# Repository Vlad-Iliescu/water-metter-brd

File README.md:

# water-metter-brd 

full board for capturing water meter image and sending it via wi-fi

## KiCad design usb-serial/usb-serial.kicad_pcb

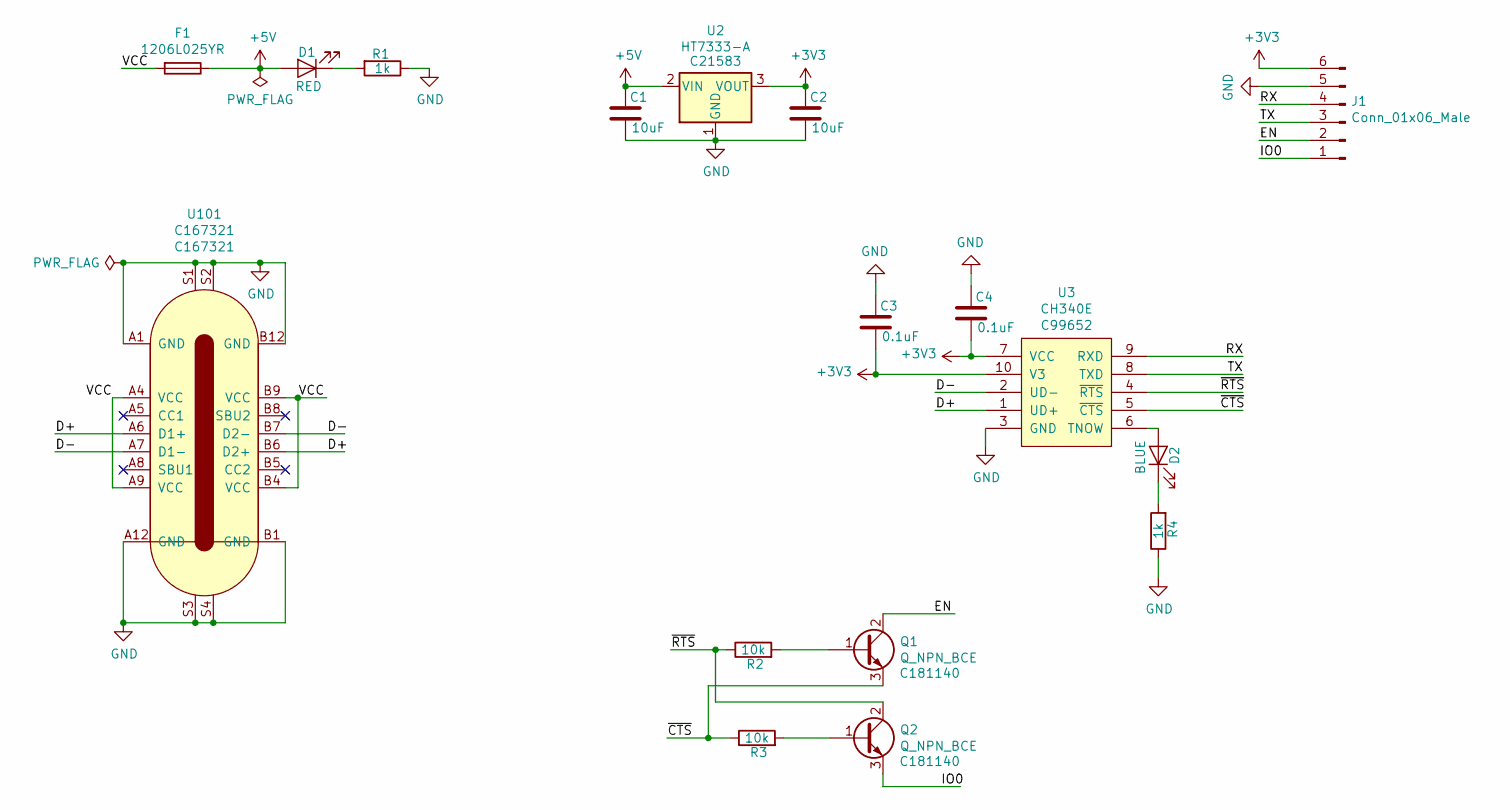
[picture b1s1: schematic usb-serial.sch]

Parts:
C1, C2: 10uF; C_0805_2012Metric
C3, C4: 0.1uF; C_0805_2012Metric
D1: RED; LED_0805_2012Metric
D2: BLUE; LED_0805_2012Metric
F1: 1206L025YR; SMD0805-020-16V; LCSC C99561
J1: Conn_01x06_Male; PinHeader_1x06_P2.54mm_Vertical
Q1, Q2: Q_NPN_BCE; SOT-23; LCSC C181140
R1, R4: 1k; R_0805_2012Metric
R2, R3: 10k; R_0805_2012Metric
U2: HT7333-A; SOT-89-3_Handsoldering; LCSC C21583
U3: CH340E; CH340E-MSOP-10; LCSC C99652
U101: C167321; LCSC C167321

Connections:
+3V3: C2.1, C3.2, C4.2, J1.6, U2.3 (VOUT), U3.7 (VCC), U3.10 (V3)
+5V: C1.1, D1.2 (A), F1.1, U2.2 (VIN)
/D+: U3.1 (UD+), U101.A6 (D1+), U101.B6 (D2+)
/D-: U3.2 (UD-), U101.A7 (D1-), U101.B7 (D2-)
/EN: J1.2, Q1.2 (C)
/IO0: J1.1, Q2.3 (E)
/RX: J1.4, U3.9 (RXD)
/TX: J1.3, U3.8 (TXD)
/VCC: F1.2, U101.A4 (VCC), U101.A9 (VCC), U101.B4 (VCC), U101.B9 (VCC)
/~CTS: Q1.3 (E), R3.1, U3.5 (~CTS~)
/~RTS: Q2.2 (C), R2.1, U3.4 (~RTS~)
GND: C1.2, C2.2, C3.1, C4.1, J1.5, R1.1, R4.1, U2.1 (GND), U3.3 (GND), U101.A1 (GND), U101.A12 (GND), U101.B1 (GND), U101.B12 (GND), U101.S1, U101.S2, U101.S3, U101.S4
unnamed: D1.1 (K), R1.2
unnamed: D2.1 (K), R4.2
unnamed: D2.2 (A), U3.6 (TNOW)
unnamed: Q1.1 (B), R2.2
unnamed: Q2.1 (B), R3.2

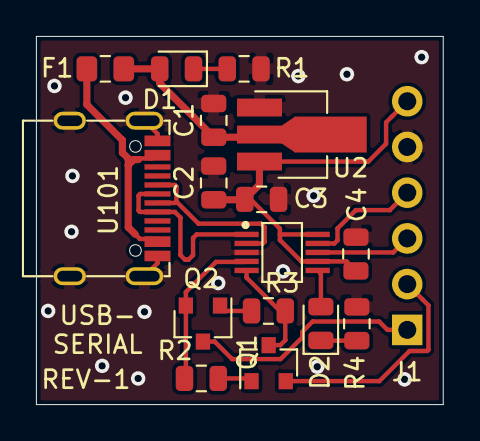
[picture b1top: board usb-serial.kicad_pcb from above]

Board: 2 copper layers, 22.6 x 20.5 mm, 17 parts (1 on the bottom side), 17 nets.

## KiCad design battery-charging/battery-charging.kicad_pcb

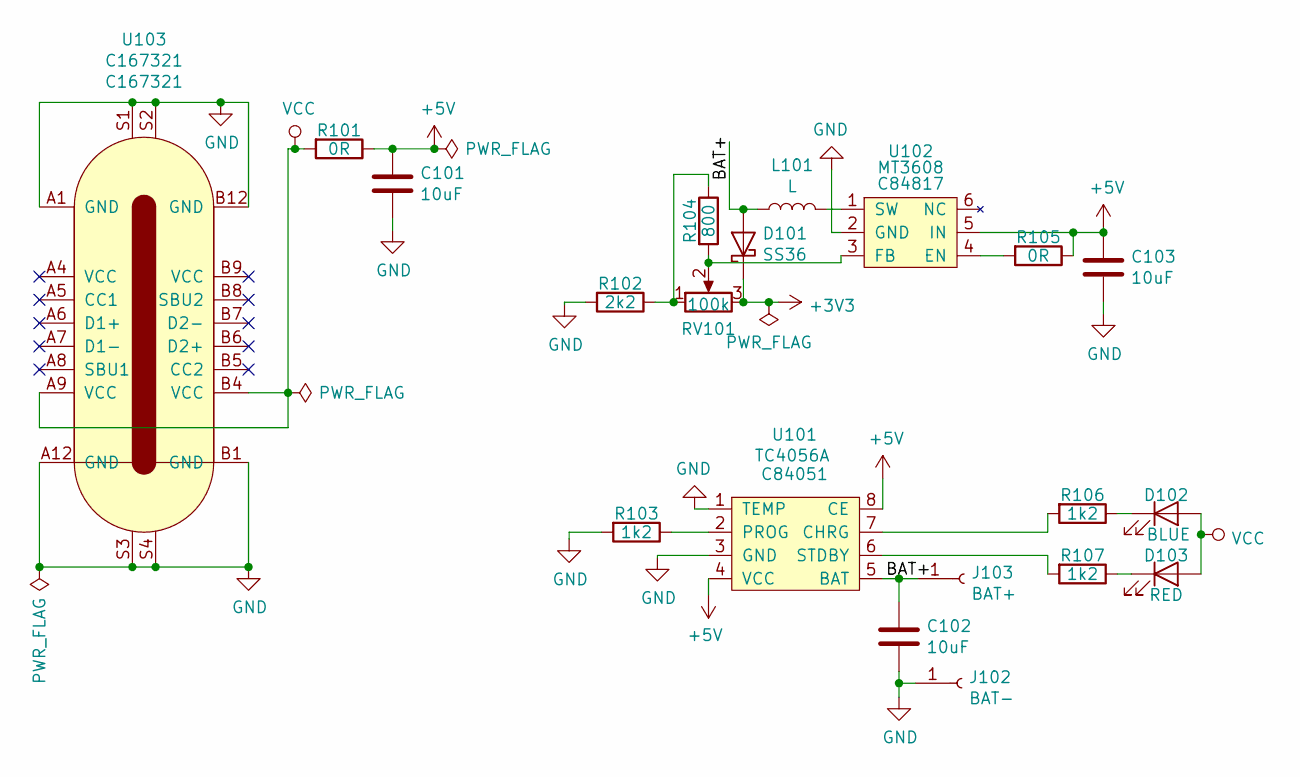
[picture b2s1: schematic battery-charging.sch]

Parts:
C101, C102, C103: 10uF; C_0805_2012Metric_Pad1.15x1.40mm_HandSolder
D101: SS36; D_SMA
D102: BLUE; LED_0805_2012Metric_Pad1.15x1.40mm_HandSolder
D103: RED; LED_0805_2012Metric_Pad1.15x1.40mm_HandSolder
J102: BAT-; PinHeader_1x01_P1.27mm_Vertical
J103: BAT+; PinHeader_1x01_P1.27mm_Vertical
L101: L; L_6.3x6.3_H3
R101, R105: 0R; R_0805_2012Metric_Pad1.15x1.40mm_HandSolder
R102: 2k2; R_0805_2012Metric_Pad1.15x1.40mm_HandSolder
R103, R106, R107: 1k2; R_0805_2012Metric_Pad1.15x1.40mm_HandSolder
R104: 800; R_0805_2012Metric_Pad1.15x1.40mm_HandSolder
RV101: 100k; Potentiometer_Bourns_3296W_Vertical
U101: TC4056A; SOP-8-1EP_4.57x4.57mm_P1.27mm_EP4.57x4.45mm_ThermalVias; LCSC C84051
U102: MT3608; SOT-23-6_Handsoldering; LCSC C84817
U103: C167321; LCSC C167321

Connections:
+3V3: D101.1 (K), RV101.3
+5V: C101.1, C103.1, R101.1, R105.1, U101.4 (VCC), U101.8 (CE), U102.5 (IN)
/BAT+: C102.1, D101.2 (A), J103.1, L101.1, U101.5 (BAT)
GND: C101.2, C102.2, C103.2, J102.1, R102.2, R103.2, U101.1 (TEMP), U101.3 (GND), U102.2 (GND), U103.A1 (GND), U103.A12 (GND), U103.B1 (GND), U103.B12 (GND), U103.S1, U103.S2, U103.S3, U103.S4
unnamed: D102.1 (K), R106.1
unnamed: D103.1 (K), R107.1
unnamed: L101.2, U102.1 (SW)
unnamed: R102.1, R104.1, RV101.1
unnamed: R103.1, U101.2 (PROG)
unnamed: R104.2, RV101.2, U102.3 (FB)
unnamed: R105.2, U102.4 (EN)
unnamed: R106.2, U101.7 (CHRG)
unnamed: R107.2, U101.6 (STDBY)
VCC: D102.2 (A), D103.2 (A), R101.2, U103.A9 (VCC), U103.B4 (VCC)

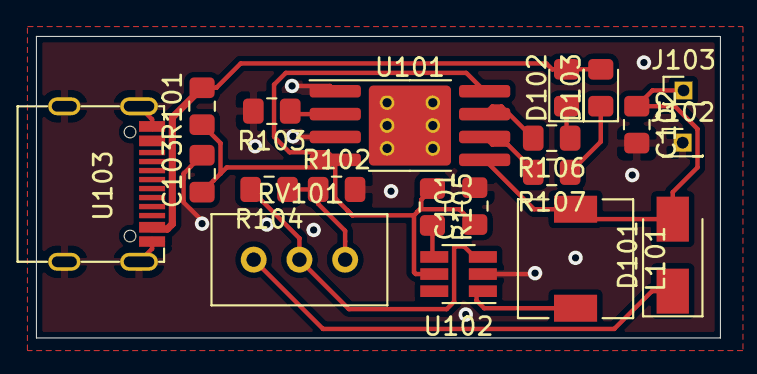
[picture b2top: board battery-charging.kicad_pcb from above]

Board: 2 copper layers, 38.0 x 16.8 mm, 20 parts (0 on the bottom side), 14 nets.

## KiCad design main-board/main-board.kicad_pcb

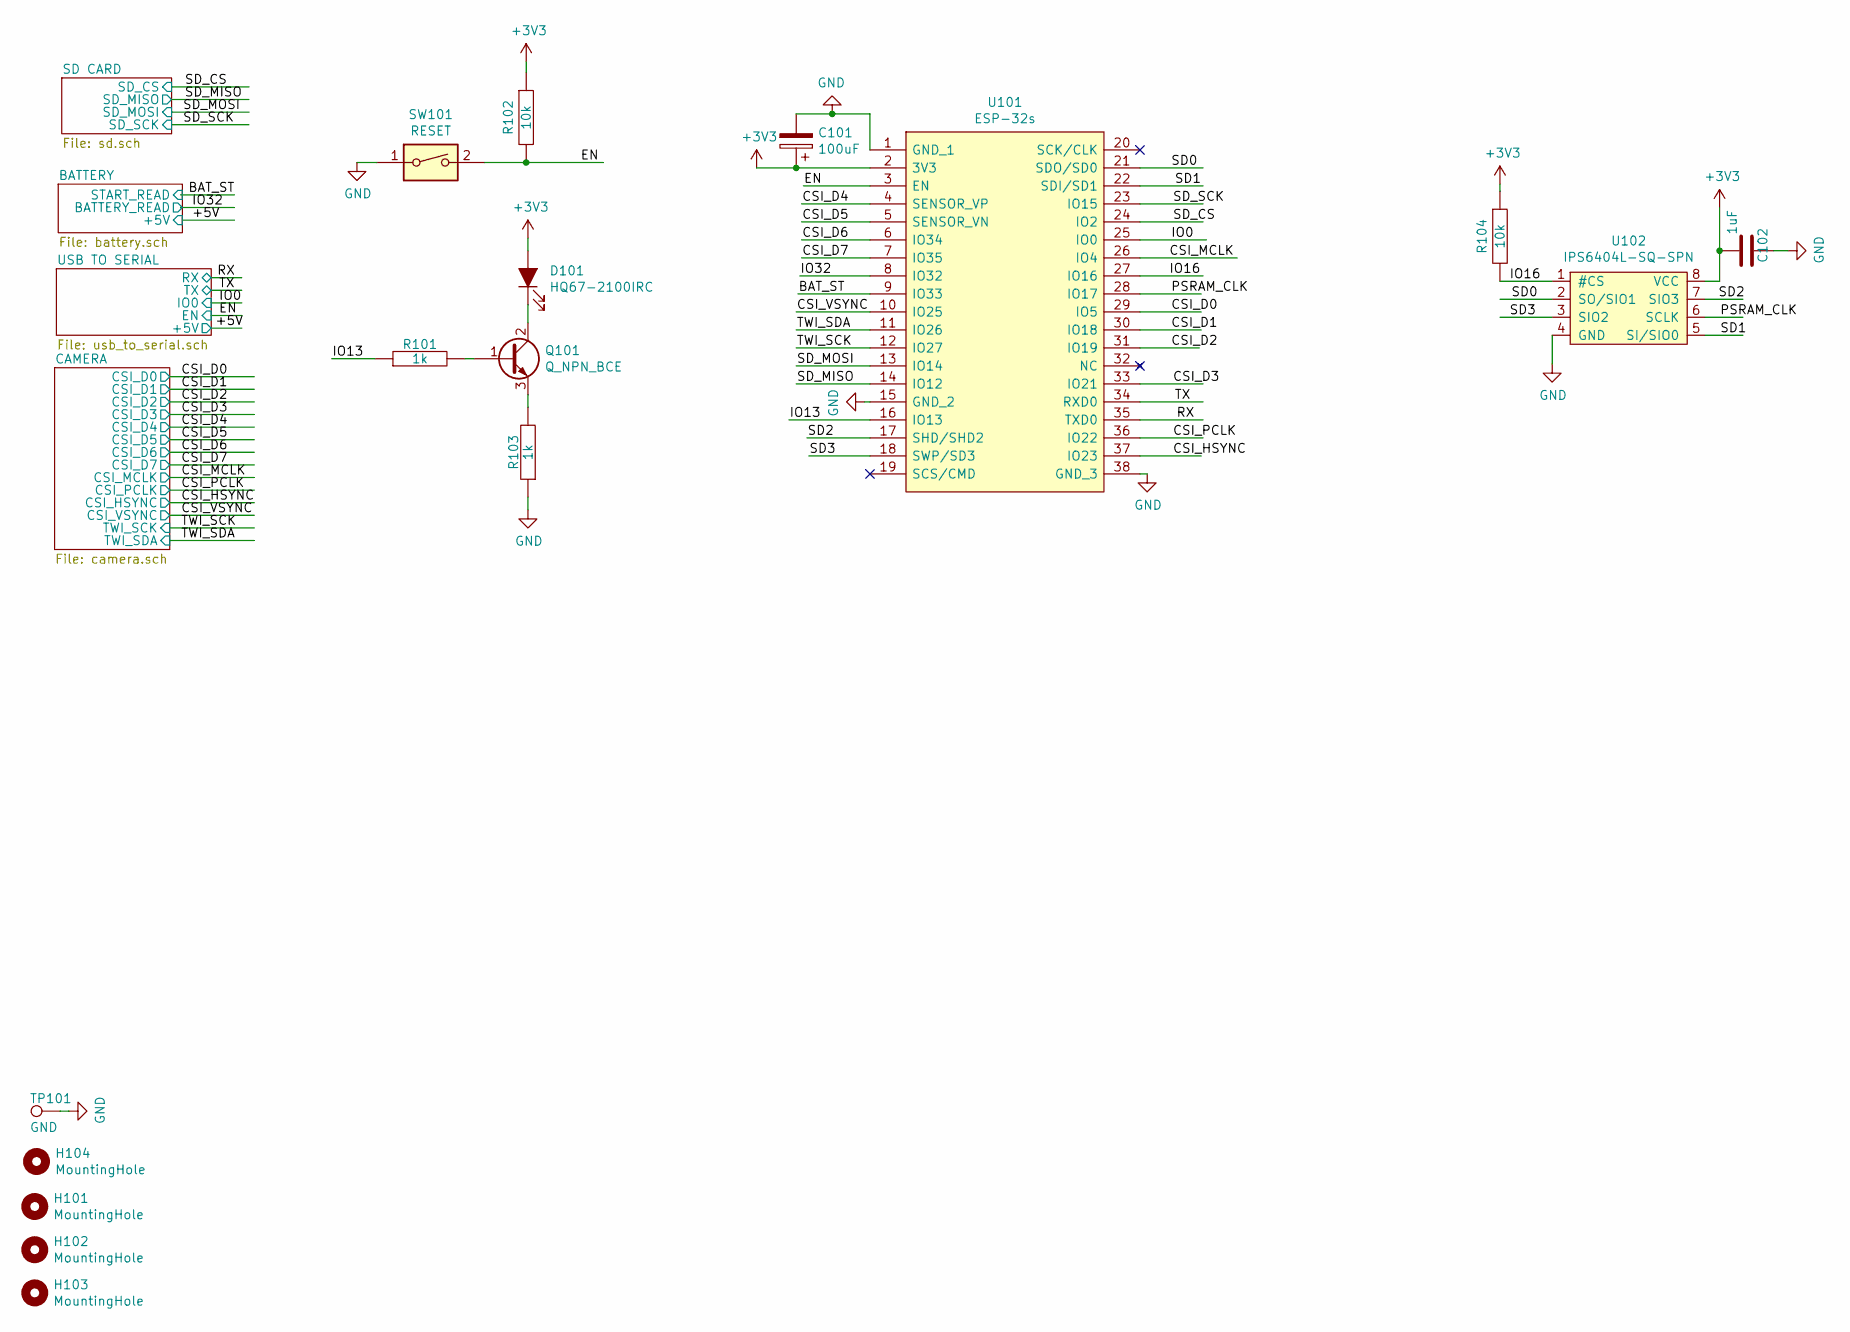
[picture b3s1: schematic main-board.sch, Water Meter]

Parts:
C101: 100uF; TAJB107M010RNJ; LCSC C7196
C102: 1uF; C_0805_2012Metric_Pad1.15x1.40mm_HandSolder; LCSC C24123
D101: HQ67-2100IRC; LCSC C258876
H101, H102, H103, H104: MountingHole; MountingHole_3.2mm_M3_Pad_Via
Q101: Q_NPN_BCE; SOT-23; LCSC C2146
R101, R103: 1k; R_0805_2012Metric_Pad1.15x1.40mm_HandSolder; LCSC C79496
R102, R104: 10k; R_0805_2012Metric_Pad1.15x1.40mm_HandSolder; LCSC C180849
SW101: RESET; SW_SPST_B3U-1000P; LCSC C231329
TP101: GND; TestPoint_Pad_D1.0mm
U101: ESP-32s; ESP-32S; Manufacturer_Part_Number ESP-32s; LCSC C277944
U102: IPS6404L-SQ-SPN; SOP-8_3.76x4.96mm_P1.27mm

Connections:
+3V3: C101.1, C102.2, D101.2 (A), R102.1, R104.1, U101.2 (3V3), U102.8 (VCC); also elsewhere on the board
/BAT_ST: U101.9 (IO33)
/CSI_D0: U101.29 (IO5); also elsewhere on the board
/CSI_D1: U101.30 (IO18); also elsewhere on the board
/CSI_D2: U101.31 (IO19); also elsewhere on the board
/CSI_D3: U101.33 (IO21); also elsewhere on the board
/CSI_D4: U101.4 (SENSOR_VP); also elsewhere on the board
/CSI_D5: U101.5 (SENSOR_VN); also elsewhere on the board
/CSI_D6: U101.6 (IO34); also elsewhere on the board
/CSI_D7: U101.7 (IO35); also elsewhere on the board
/CSI_HSYNC: U101.37 (IO23); also elsewhere on the board
/CSI_MCLK: U101.26 (IO4); also elsewhere on the board
/CSI_PCLK: U101.36 (IO22); also elsewhere on the board
/CSI_VSYNC: U101.10 (IO25); also elsewhere on the board
/EN: R102.2, SW101.2, U101.3 (EN); also elsewhere on the board
/IO0: U101.25 (IO0); also elsewhere on the board
/IO13: R101.1, U101.16 (IO13)
/IO16: R104.2, U101.27 (IO16), U102.1 (#CS)
/IO32: U101.8 (IO32)
/PSRAM_CLK: U101.28 (IO17), U102.6 (SCLK)
/RX: U101.35 (TXD0); also elsewhere on the board
/SD0: U101.21 (SDO/SD0), U102.2 (SO/SIO1)
/SD1: U101.22 (SDI/SD1), U102.5 (SI/SIO0)
/SD2: U101.17 (SHD/SHD2), U102.7 (SIO3)
/SD3: U101.18 (SWP/SD3), U102.3 (SIO2)
/SD_CS: U101.24 (IO2); also elsewhere on the board
/SD_MISO: U101.14 (IO12); also elsewhere on the board
/SD_MOSI: U101.13 (IO14); also elsewhere on the board
/SD_SCK: U101.23 (IO15); also elsewhere on the board
/TWI_SCK: U101.12 (IO27); also elsewhere on the board
/TWI_SDA: U101.11 (IO26); also elsewhere on the board
/TX: U101.34 (RXD0); also elsewhere on the board
GND: C101.2, C102.1, R103.1, SW101.1, TP101.1, U101.1 (GND_1), U101.15 (GND_2), U101.38 (GND_3), U102.4 (GND); also elsewhere on the board
unnamed: D101.1 (K), Q101.2 (C)
unnamed: Q101.1 (B), R101.2
unnamed: Q101.3 (E), R103.2

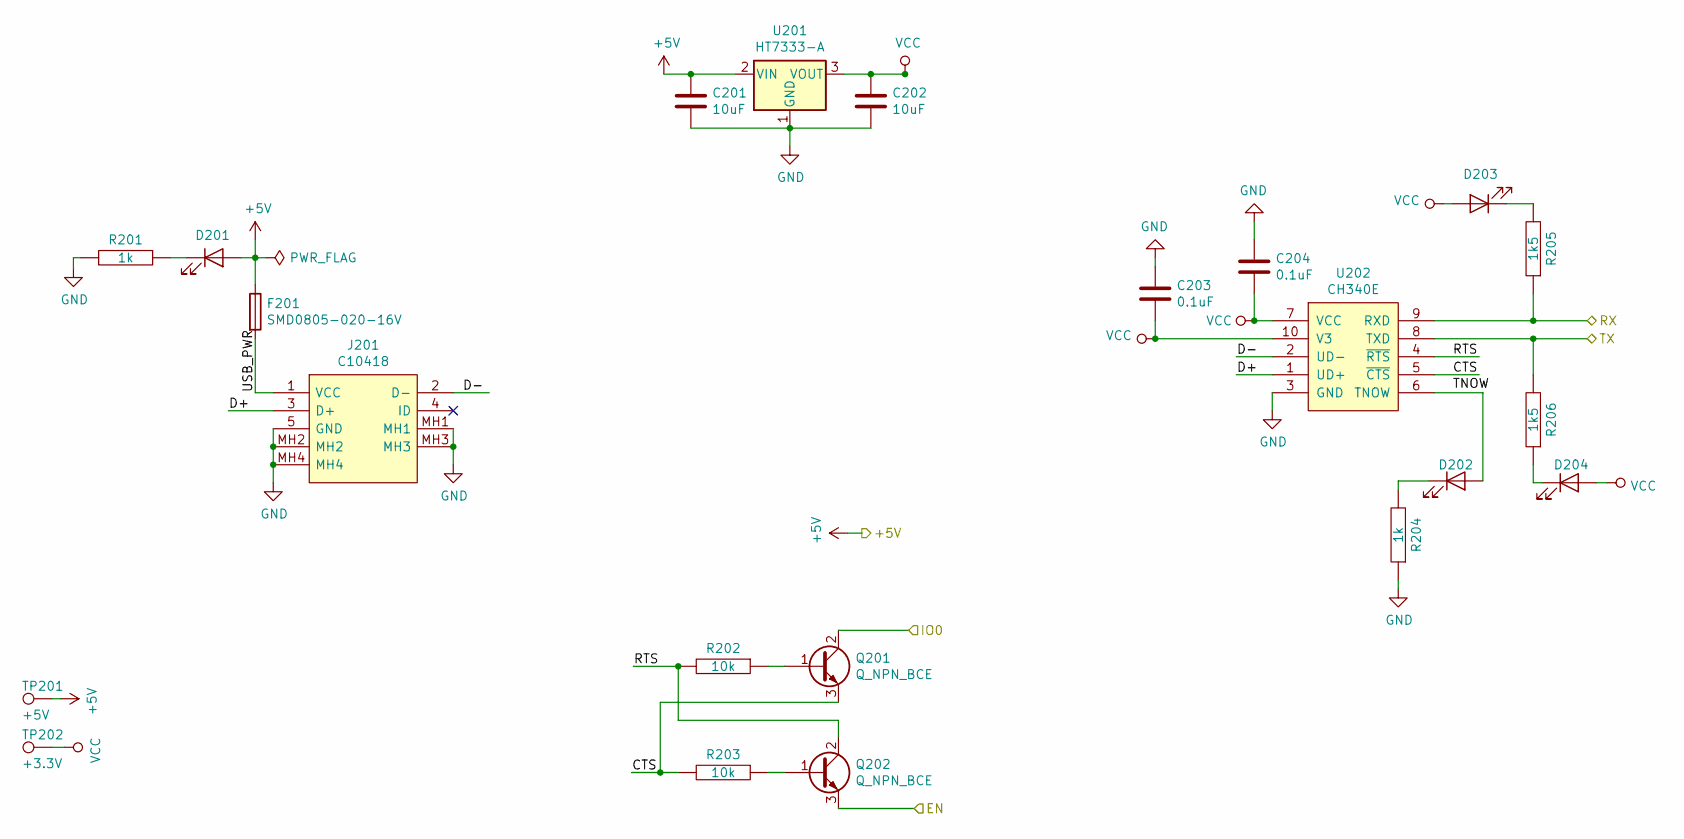
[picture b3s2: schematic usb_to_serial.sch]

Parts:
C201, C202: 10uF; C_0805_2012Metric_Pad1.15x1.40mm_HandSolder; LCSC C15850
C203, C204: 0.1uF; C_0805_2012Metric_Pad1.15x1.40mm_HandSolder; LCSC C1790
D201, D202, D203, D204: LED; LED_0805_2012Metric_Pad1.15x1.40mm_HandSolder; LCSC C94691
F201: SMD0805-020-16V; Fuse_0805_2012Metric_Pad1.15x1.40mm_HandSolder; LCSC C99561
J201: C10418; Manufacturer_Part_Number C10418; LCSC C10418
Q201, Q202: Q_NPN_BCE; SOT-23; LCSC C181140
R201, R204: 1k; R_0805_2012Metric_Pad1.15x1.40mm_HandSolder; LCSC C79496
R202, R203: 10k; R_0805_2012Metric_Pad1.15x1.40mm_HandSolder; LCSC C180849
R205, R206: 1k5; R_0805_2012Metric_Pad1.15x1.40mm_HandSolder; LCSC C336856
TP201: +5V; TestPoint_Pad_D1.0mm
TP202: +3.3V; TestPoint_Pad_D1.0mm
U201: HT7333-A; SOT-89-3_Handsoldering; LCSC C21583
U202: CH340E; CH340E-MSOP-10; LCSC C99652

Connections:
+5V: C201.1, D201.2 (A), F201.1, TP201.1, U201.2 (VIN); also elsewhere on the board
/EN: Q202.3 (E); also elsewhere on the board
/IO0: Q201.2 (C); also elsewhere on the board
/RX: R205.1, U202.9 (RXD); also elsewhere on the board
/TX: R206.2, U202.8 (TXD); also elsewhere on the board
/USB TO SERIAL/CTS: Q201.3 (E), R203.2, U202.5 (~CTS~)
/USB TO SERIAL/D+: J201.3 (D+), U202.1 (UD+)
/USB TO SERIAL/D-: J201.2 (D-), U202.2 (UD-)
/USB TO SERIAL/RTS: Q202.2 (C), R202.2, U202.4 (~RTS~)
/USB TO SERIAL/USB_PWR: F201.2, J201.1 (VCC)
GND: C201.2, C202.2, C203.1, C204.1, J201.5 (GND), J201.MH1, J201.MH2, J201.MH3, J201.MH4, R201.2, R204.1, U201.1 (GND), U202.3 (GND); also elsewhere on the board
unnamed: D201.1 (K), R201.1
unnamed: D202.1 (K), R204.2
unnamed: D202.2 (A), U202.6 (TNOW)
unnamed: D203.1 (K), R205.2
unnamed: D204.1 (K), R206.1
unnamed: Q201.1 (B), R202.1
unnamed: Q202.1 (B), R203.1
VCC: C202.1, C203.2, C204.2, D203.2 (A), D204.2 (A), TP202.1, U201.3 (VOUT), U202.7 (VCC), U202.10 (V3)

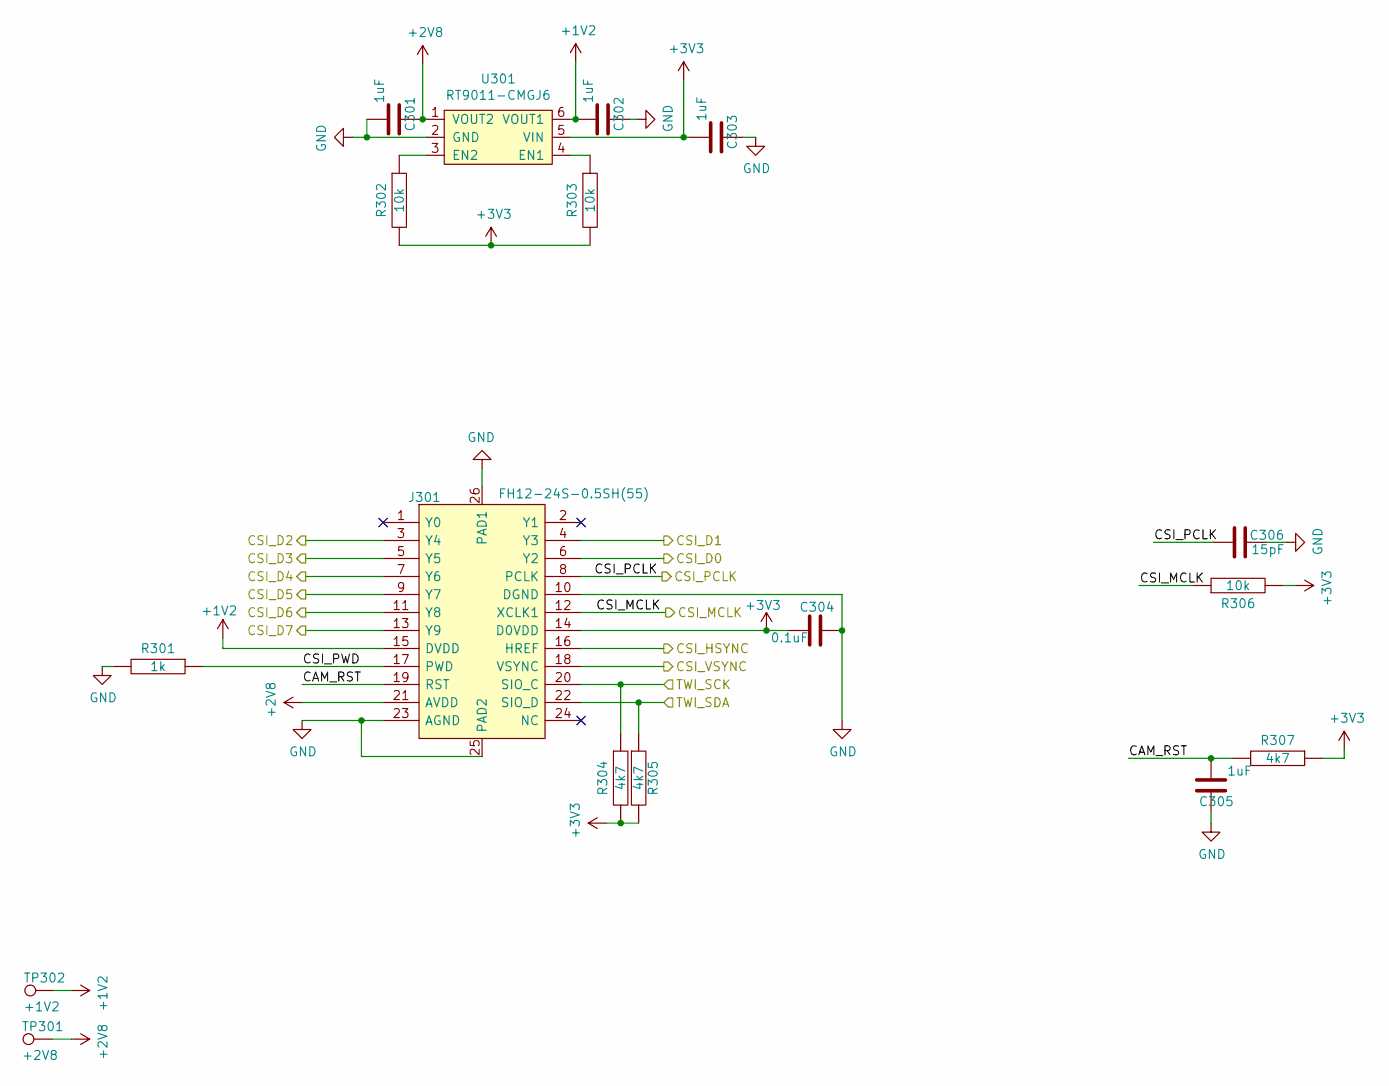
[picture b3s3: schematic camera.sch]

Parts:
C301, C302, C303, C305: 1uF; C_0805_2012Metric_Pad1.15x1.40mm_HandSolder; LCSC C24123
C304: 0.1uF; C_0805_2012Metric_Pad1.15x1.40mm_HandSolder; LCSC C1790
C306: 15pF; C_0805_2012Metric_Pad1.15x1.40mm_HandSolder; LCSC C1794
J301: FH12-24S-0.5SH(55); Manufacturer_Part_Number FH12-24S-0.5SH(55); LCSC Part Number C202112
R301: 1k; R_0805_2012Metric_Pad1.15x1.40mm_HandSolder; LCSC C79496
R302, R303, R306: 10k; R_0805_2012Metric_Pad1.15x1.40mm_HandSolder; LCSC C180849
R304, R305, R307: 4k7; R_0805_2012Metric_Pad1.15x1.40mm_HandSolder; LCSC C336873
TP301: +2V8; TestPoint_Pad_D1.0mm
TP302: +1V2; TestPoint_Pad_D1.0mm
U301: RT9011-CMGJ6; SOT-23-6_Handsoldering; LCSC C131424

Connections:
+1V2: C302.2, J301.15 (DVDD), TP302.1, U301.6 (VOUT1)
+2V8: C301.1, J301.21 (AVDD), TP301.1, U301.1 (VOUT2)
+3V3: C303.2, C304.2, J301.14 (D0VDD), R302.2, R303.2, R304.2, R305.2, R306.2, R307.1, U301.5 (VIN); also elsewhere on the board
/CAMERA/CAM_RST: C305.2, J301.19 (RST), R307.2
/CAMERA/CSI_PWD: J301.17 (PWD), R301.1
/CSI_D0: J301.6 (Y2); also elsewhere on the board
/CSI_D1: J301.4 (Y3); also elsewhere on the board
/CSI_D2: J301.3 (Y4); also elsewhere on the board
/CSI_D3: J301.5 (Y5); also elsewhere on the board
/CSI_D4: J301.7 (Y6); also elsewhere on the board
/CSI_D5: J301.9 (Y7); also elsewhere on the board
/CSI_D6: J301.11 (Y8); also elsewhere on the board
/CSI_D7: J301.13 (Y9); also elsewhere on the board
/CSI_HSYNC: J301.16 (HREF); also elsewhere on the board
/CSI_MCLK: J301.12 (XCLK1), R306.1; also elsewhere on the board
/CSI_PCLK: C306.2, J301.8 (PCLK); also elsewhere on the board
/CSI_VSYNC: J301.18 (VSYNC); also elsewhere on the board
/TWI_SCK: J301.20 (SIO_C), R304.1; also elsewhere on the board
/TWI_SDA: J301.22 (SIO_D), R305.1; also elsewhere on the board
GND: C301.2, C302.1, C303.1, C304.1, C305.1, C306.1, J301.10 (DGND), J301.23 (AGND), J301.25 (PAD2), J301.26 (PAD1), R301.2, U301.2 (GND); also elsewhere on the board
unnamed: R302.1, U301.3 (EN2)
unnamed: R303.1, U301.4 (EN1)

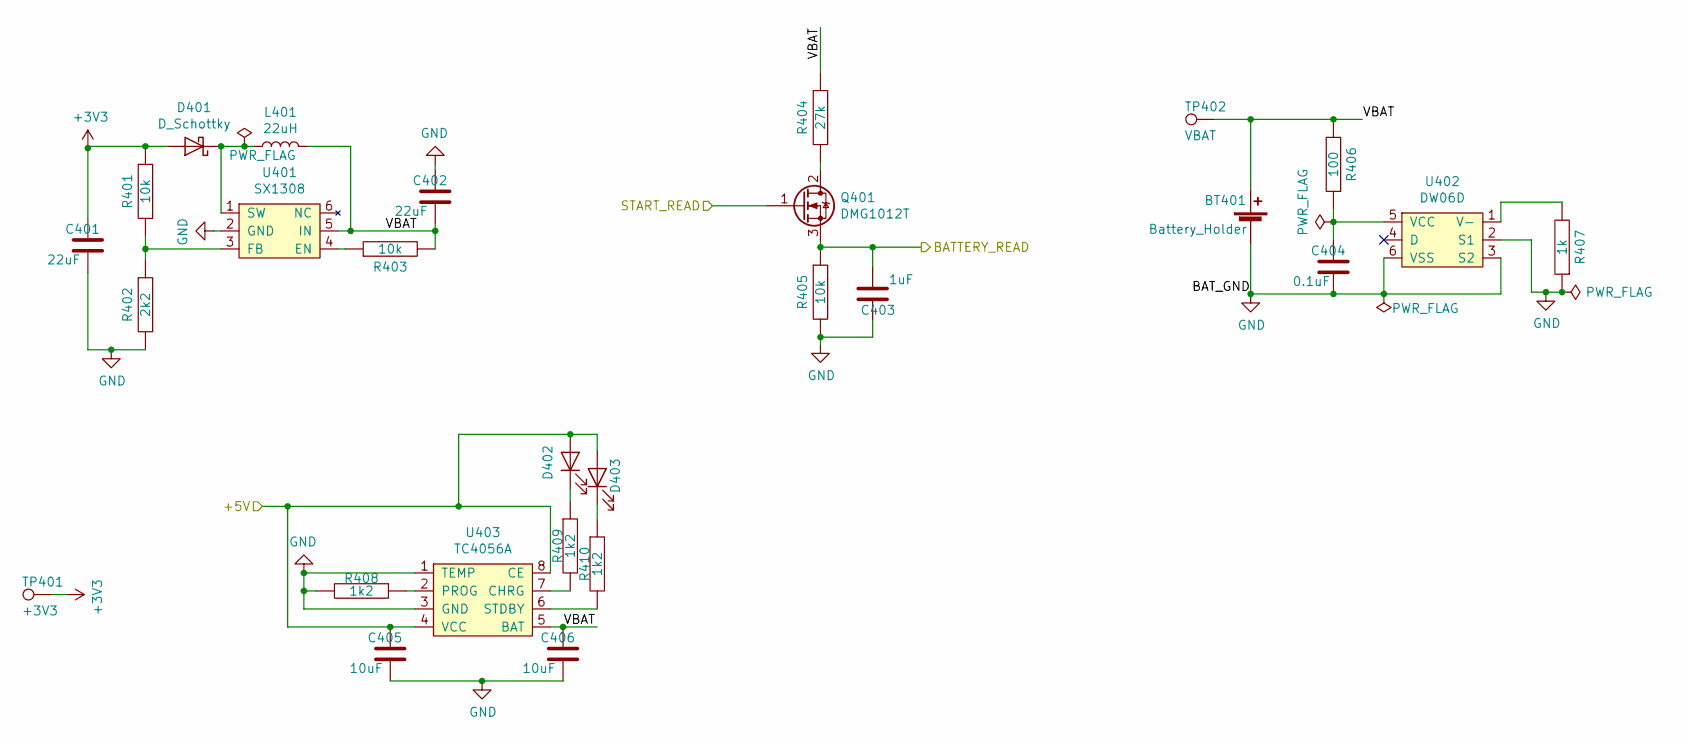
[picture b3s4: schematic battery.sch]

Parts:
BT401: Battery_Holder; Battery-Holder-SMD
C401, C402: 22uF; C_1206_3216Metric_Pad1.42x1.75mm_HandSolder; LCSC C87996
C403: 1uF; C_0805_2012Metric_Pad1.15x1.40mm_HandSolder; LCSC C24123
C404: 0.1uF; C_0805_2012Metric_Pad1.15x1.40mm_HandSolder; LCSC C1790
C405, C406: 10uF; C_1206_3216Metric_Pad1.42x1.75mm_HandSolder; LCSC C87996
D401: D_Schottky; D_SMA_Handsoldering; LCSC C274651
D402: RED; LED_0805_2012Metric_Pad1.15x1.40mm_HandSolder; LCSC C94691
D403: GREEN; LED_0805_2012Metric_Pad1.15x1.40mm_HandSolder; LCSC C94691
L401: 22uH; L_Bourns-SRN6028; LCSC C266430
Q401: DMG1012T; SOT-523; LCSC C20512
R401, R403, R405: 10k; R_0805_2012Metric_Pad1.15x1.40mm_HandSolder; LCSC C180849
R402: 2k2; R_0805_2012Metric_Pad1.15x1.40mm_HandSolder; LCSC C203855
R404: 27k; R_0805_2012Metric_Pad1.15x1.40mm_HandSolder; LCSC C317283
R406: 100; R_0805_2012Metric_Pad1.15x1.40mm_HandSolder; LCSC C230647
R407: 1k; R_0805_2012Metric_Pad1.15x1.40mm_HandSolder; LCSC C79496
R408, R409, R410: 1k2; R_0805_2012Metric_Pad1.15x1.40mm_HandSolder; LCSC C180849
TP401: +3V3; TestPoint_Pad_D1.0mm
TP402: VBAT; TestPoint_Pad_D1.0mm
U401: SX1308; SOT-23-6_Handsoldering; LCSC C78162
U402: DW06D; SOT-23-6_Handsoldering; LCSC C82123
U403: TC4056A; SOP-8-1EP_4.57x4.57mm_P1.27mm_EP4.57x4.45mm_ThermalVias; LCSC C84051

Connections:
+3V3: C401.1, D401.2 (A), R401.1, TP401.1; also elsewhere on the board
+5V: C405.1, D402.2 (A), D403.2 (A), U403.4 (VCC), U403.8 (CE); also elsewhere on the board
/BATTERY/BATTERY_READ: C403.2, Q401.3 (S), R405.1
/BATTERY/START_READ: Q401.1 (G)
/BATTERY/VBAT: BT401.+, C402.2, C406.1, L401.2, R403.2, R404.1, R406.2, TP402.1, U401.5 (IN), U403.5 (BAT)
GND: BT401.-, C401.2, C402.1, C403.1, C404.2, C405.2, C406.2, R402.2, R405.2, R407.1, R408.2, U401.2 (GND), U402.2 (S1), U402.3 (S2), U402.6 (VSS), U403.1 (TEMP), U403.3 (GND); also elsewhere on the board
unnamed: C404.1, R406.1, U402.5 (VCC)
unnamed: D401.1 (K), L401.1, U401.1 (SW)
unnamed: D402.1 (K), R409.1
unnamed: D403.1 (K), R410.1
unnamed: Q401.2 (D), R404.2
unnamed: R401.2, R402.1, U401.3 (FB)
unnamed: R403.1, U401.4 (EN)
unnamed: R407.2, U402.1 (V-)
unnamed: R408.1, U403.2 (PROG)
unnamed: R409.2, U403.7 (CHRG)
unnamed: R410.2, U403.6 (STDBY)

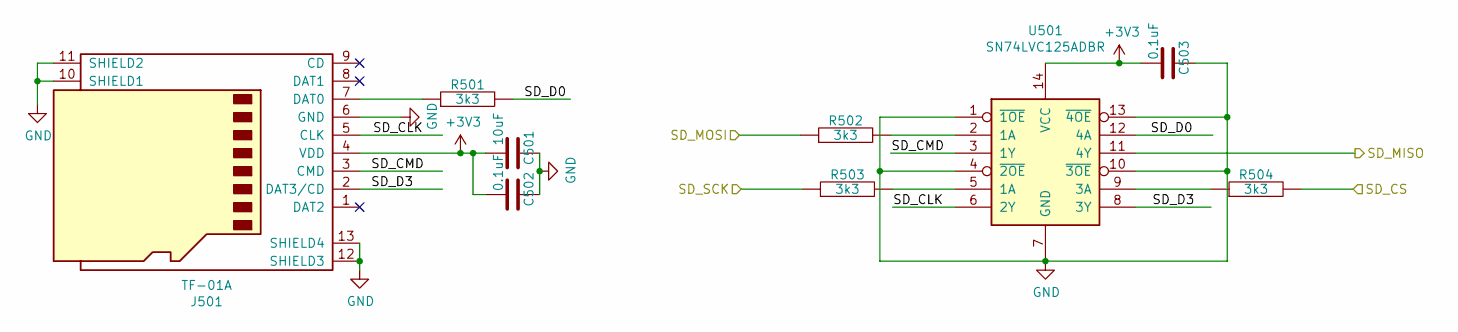
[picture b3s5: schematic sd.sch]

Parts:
C501: 10uF; C_0805_2012Metric_Pad1.15x1.40mm_HandSolder; LCSC C15850
C502, C503: 0.1uF; C_0805_2012Metric_Pad1.15x1.40mm_HandSolder; LCSC C1790
J501: TF-01A; LCSC C91145
R501, R502, R503, R504: 3k3; R_0805_2012Metric_Pad1.15x1.40mm_HandSolder; LCSC C160077
U501: SN74LVC125ADBR; TSSOP-14_4.4x5mm_P0.65mm; LCSC C7812

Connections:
+3V3: C501.2, C502.2, C503.2, J501.4 (VDD), U501.14 (VCC); also elsewhere on the board
/SD CARD/SD_CLK: J501.5 (CLK), U501.6 (2Y)
/SD CARD/SD_CMD: J501.3 (CMD), U501.3 (1Y)
/SD CARD/SD_D0: R501.2, U501.12 (4A)
/SD CARD/SD_D3: J501.2 (DAT3/CD), U501.8 (3Y)
/SD_CS: R504.2; also elsewhere on the board
/SD_MISO: U501.11 (4Y); also elsewhere on the board
/SD_MOSI: R502.1; also elsewhere on the board
/SD_SCK: R503.1; also elsewhere on the board
GND: C501.1, C502.1, C503.1, J501.6 (GND), J501.10 (SHIELD1), J501.11 (SHIELD2), J501.12 (SHIELD3), J501.13 (SHIELD4), U501.1 (~1OE), U501.4 (~2OE), U501.7 (GND), U501.10 (~3OE), U501.13 (~4OE); also elsewhere on the board
unnamed: J501.7 (DAT0), R501.1
unnamed: R502.2, U501.2 (1A)
unnamed: R503.2, U501.5 (1A)
unnamed: R504.1, U501.9 (3A)

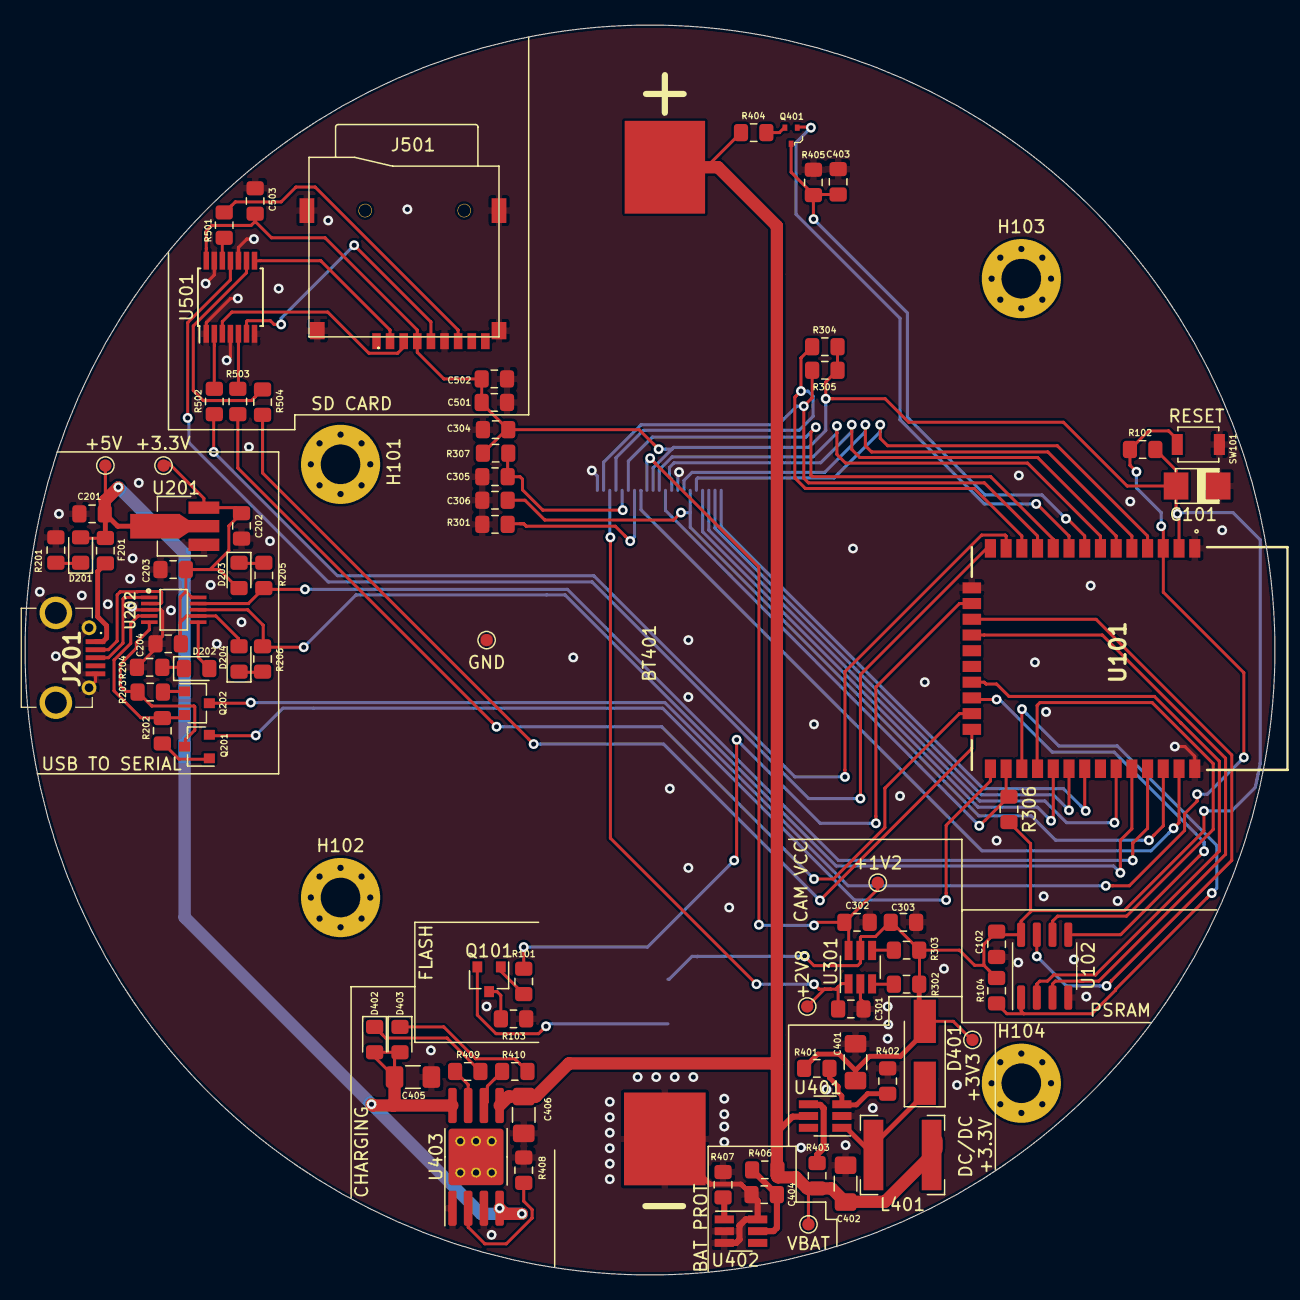
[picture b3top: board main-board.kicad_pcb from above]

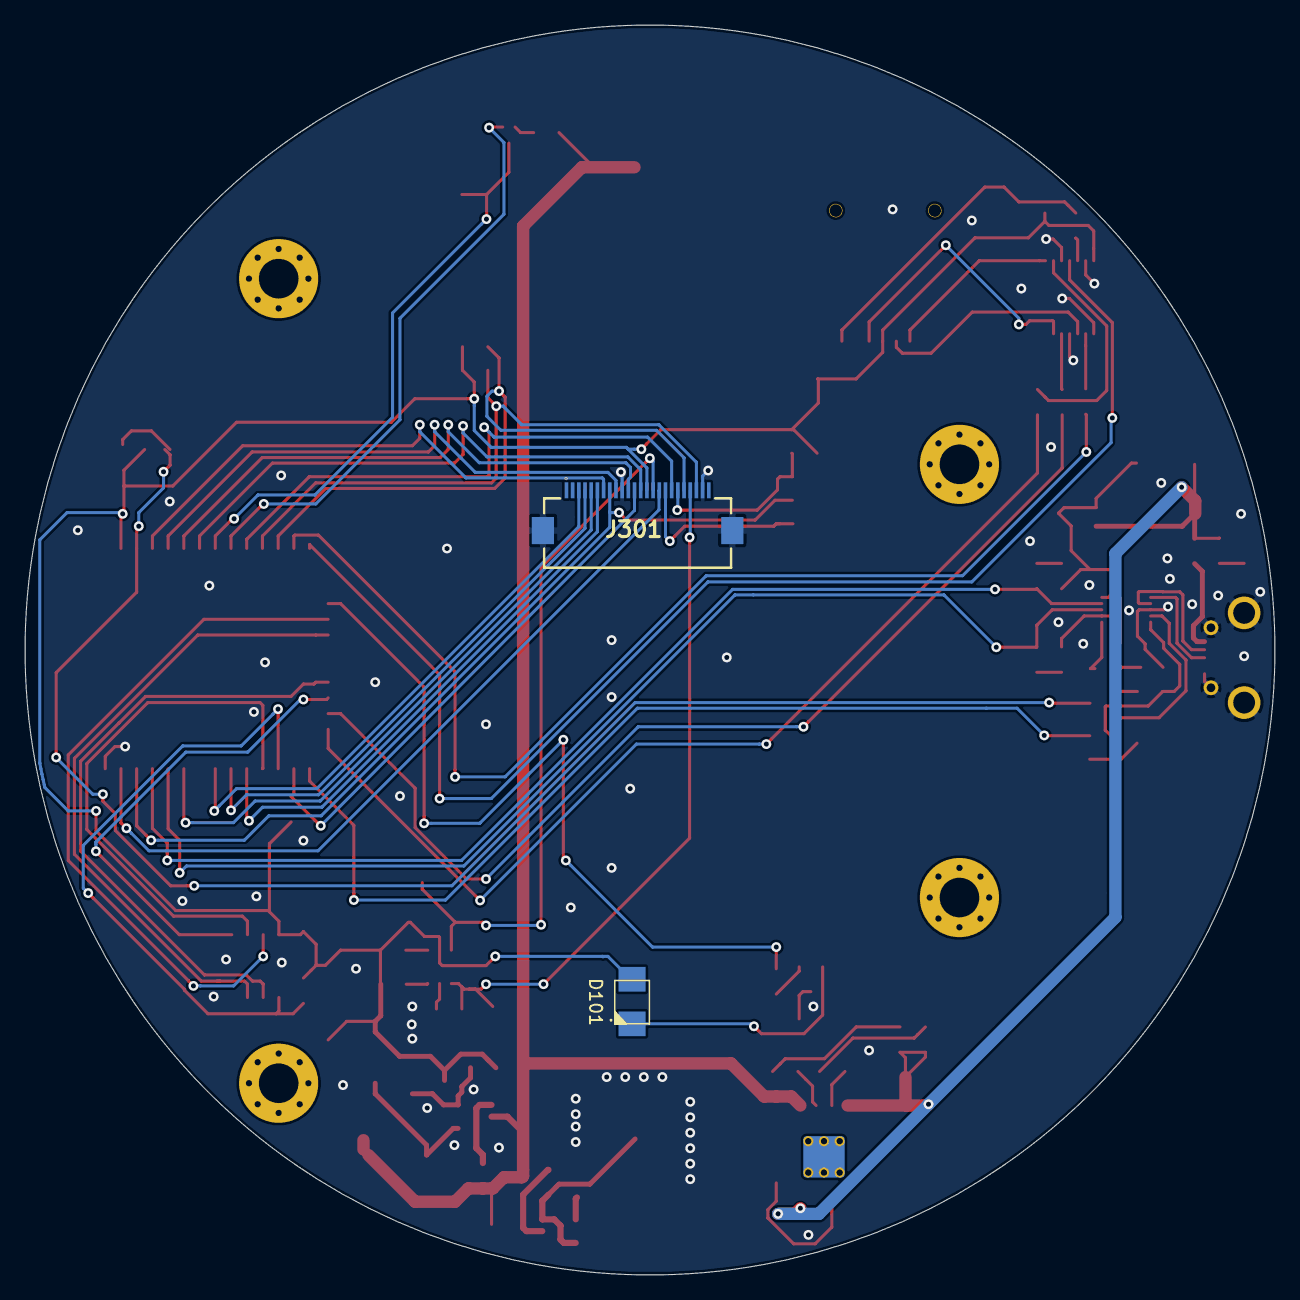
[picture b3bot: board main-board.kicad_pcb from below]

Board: 2 copper layers, 101.0 x 101.0 mm, 91 parts (2 on the bottom side), 75 nets.

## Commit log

2019-08-16 parts update
2019-08-17 5v dc/dc
2019-09-06 Added new components
2019-09-06 USB to Serial
2019-09-25 USB to Serial done
2019-09-25 Added FUse 0805 to lib
2019-09-25 Added pin header
2019-09-26 Added schema and board pdf/png + Readme
2019-09-30 Added USB-Serial to main design
2019-09-30 Added PSRAM
2019-10-01 CAM ribbon connection
2019-10-02 KiCad start
2019-10-02 battery holder
2019-10-03 battery protection + buckboost
2019-10-04 boost, LDOs, ribbon connerctions
2019-10-05 ribbon connections and reset sw
2019-10-05 removed .DS_Store
2019-10-05 updated gitignore
2019-10-05 SD card
2019-10-06 SD passive and wires
2019-10-07 LED and few connection
2019-10-07 LED SMD
2019-10-07 DRC Fix
2019-10-07 SD Slot Fix
2019-10-07 Small fixes
2019-10-08 Mounting holes and test points
2019-10-08 BOM parts
2019-10-09 BOM parts 2
2019-10-09 refactor
2019-10-10 ALPHA 1
2019-10-10 dimensions
2019-10-10 Added PDFs
2019-10-10 Added render
2019-11-02 added battery charging
2019-11-06 Smaller battery holder
2019-11-23 usb-c
2019-11-23 schematic
2019-11-24 usb-c rev-1 rc
2019-11-24 usb-c rev-1 rc1
2019-12-26 added C167321 usb c
2019-12-26 changed usb part
2020-01-06 battery changing urb c
2020-03-18 switch RTC <-> CTS
